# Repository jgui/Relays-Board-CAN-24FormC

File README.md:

# Relays-Board-CAN-24FormC
Board with 24 relays (Form C) controlled by CAN.

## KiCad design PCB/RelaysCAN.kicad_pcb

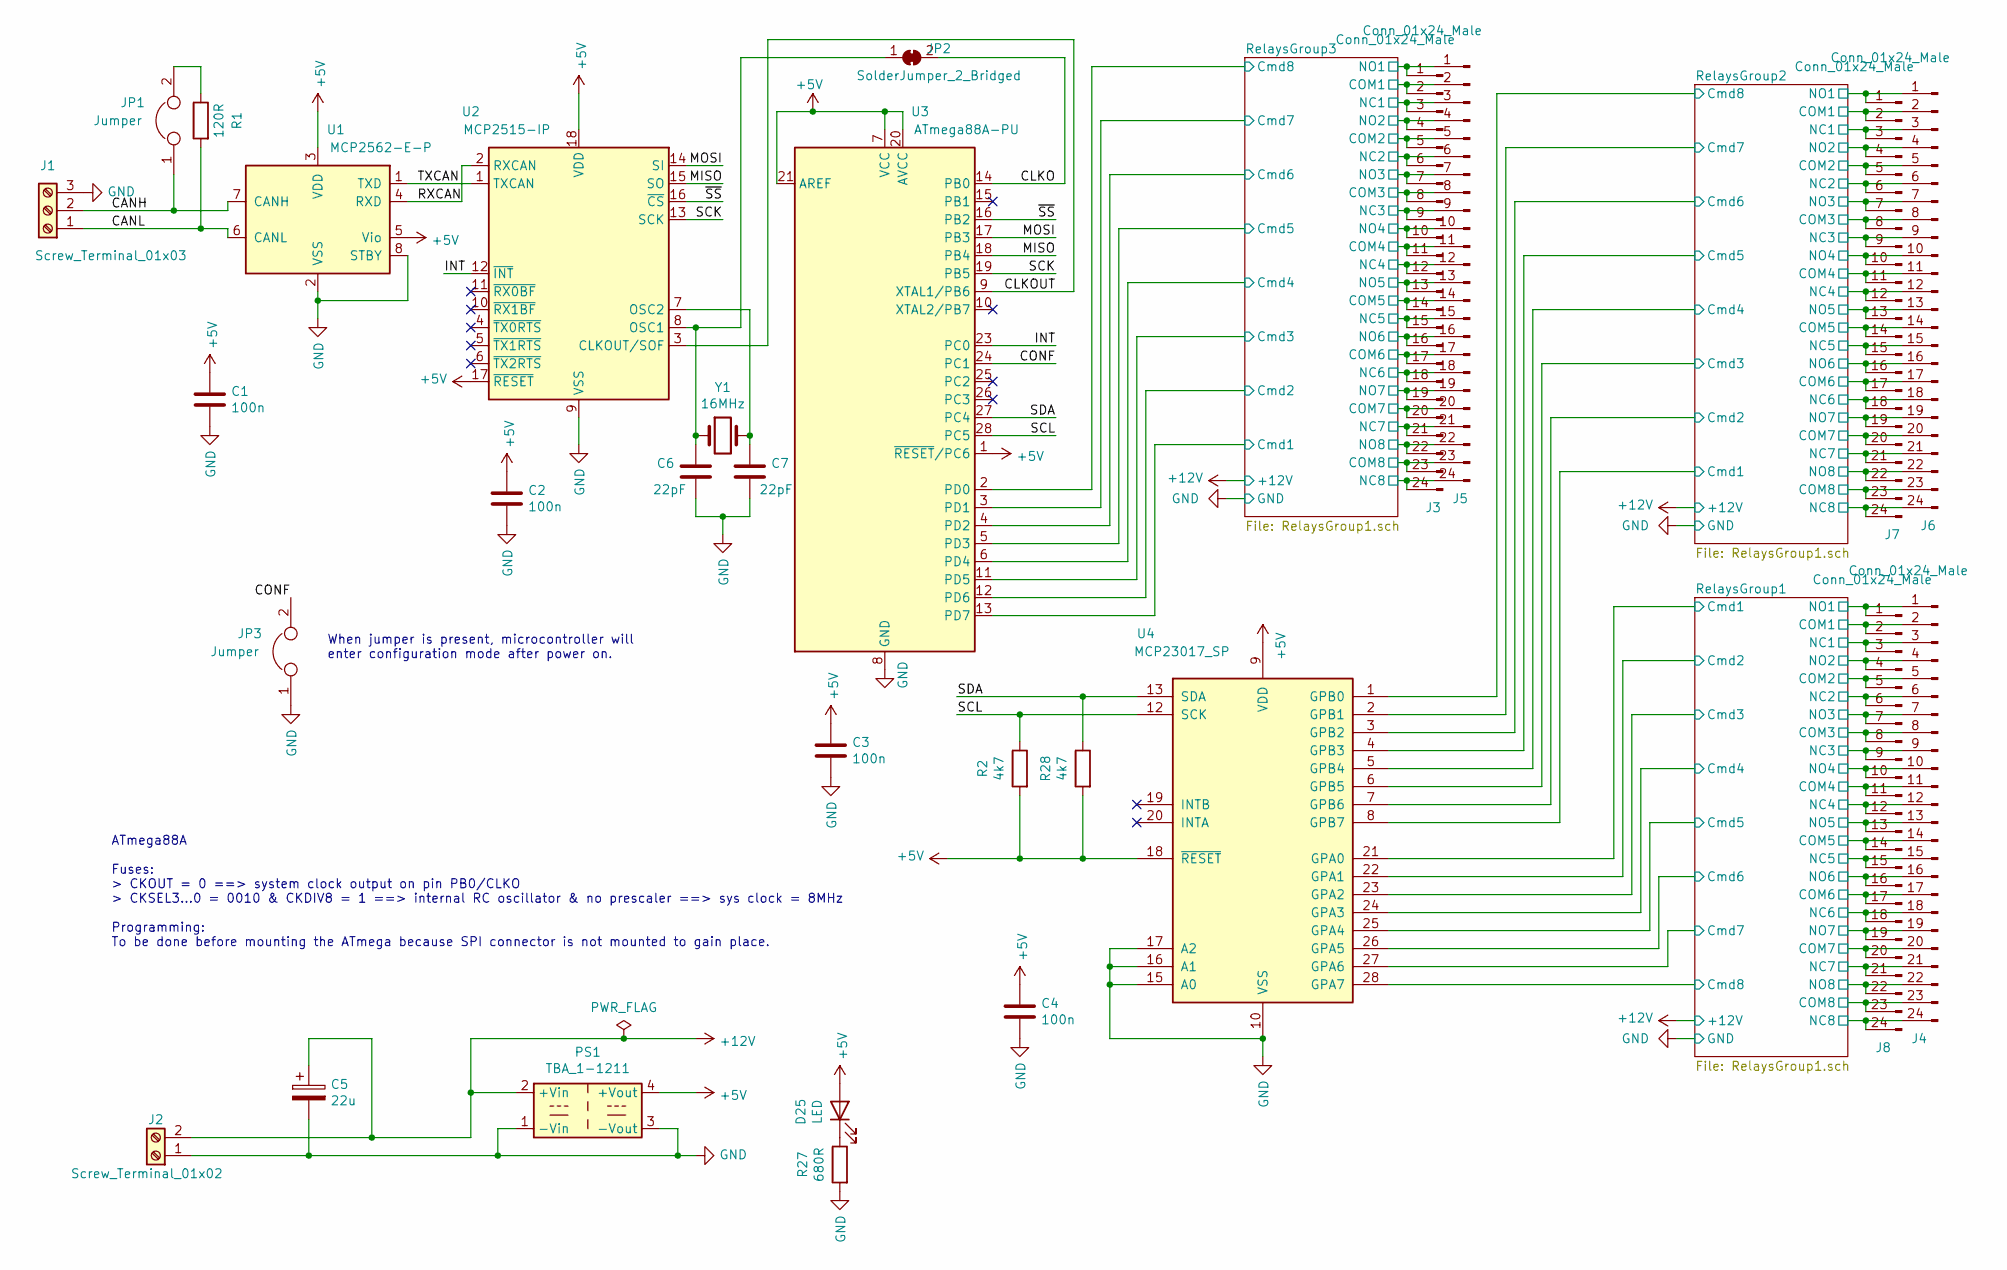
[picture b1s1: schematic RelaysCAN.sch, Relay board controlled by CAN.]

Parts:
C1, C2, C3, C4: 100n; C_Disc_D4.3mm_W1.9mm_P5.00mm
C5: 22u; CP_Radial_D5.0mm_P2.50mm
C6, C7: 22pF; C_Disc_D4.3mm_W1.9mm_P5.00mm
D25: LED; LED_D3.0mm
J1: Screw_Terminal_01x03; TerminalBlock_bornier-3_P5.08mm
J2: Screw_Terminal_01x02; TerminalBlock_bornier-2_P5.08mm
J3, J7, J8: Conn_01x24_Male; DualSideEdge_65x250mils_2.54mmx24pads
J4, J5, J6: Conn_01x24_Male; PinHeader_1x24_P2.54mm_Vertical
JP1, JP3: Jumper; PinHeader_1x02_P2.54mm_Vertical
JP2: SolderJumper_2_Bridged; SolderJumper-2_P1.3mm_Open_RoundedPad1.0x1.5mm
PS1: TBA_1-1211; Converter_DCDC_TRACO_TBA-1-xxxx_Single_THT
R1: 120R; R_Axial_DIN0207_L6.3mm_D2.5mm_P5.08mm_Vertical
R2, R28: 4k7; R_Axial_DIN0207_L6.3mm_D2.5mm_P5.08mm_Vertical
R27: 680R; R_Axial_DIN0207_L6.3mm_D2.5mm_P5.08mm_Vertical
U1: MCP2562-E-P; DIP-8_W7.62mm
U2: MCP2515-IP; DIP-18_W7.62mm_LongPads
U3: ATmega88A-PU; DIP-28_W7.62mm_LongPads
U4: MCP23017_SP; DIP-28_W7.62mm_LongPads
Y1: 16MHz; Crystal_HC18-U_Vertical

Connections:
+5V: C1.1, C2.1, C3.1, C4.1, D25.2 (A), PS1.4 (+Vout), R2.2, R28.2, U1.3 (VDD), U1.5 (Vio), U2.17 (~RESET), U2.18 (VDD), U3.1 (~RESET~/PC6), U3.7 (VCC), U3.20 (AVCC), U3.21 (AREF), U4.9 (VDD), U4.18 (~RESET~)
+12V: C5.1, J2.2, PS1.2 (+Vin); also elsewhere on the board
/CANH: J1.2, JP1.1, U1.7 (CANH)
/CANL: J1.1, R1.2, U1.6 (CANL)
/CLKO: JP2.2 (B), U3.14 (PB0)
/CLKOUT: U2.3 (CLKOUT/SOF), U3.9 (XTAL1/PB6)
/CONF: JP3.2, U3.24 (PC1)
/INT: U2.12 (~INT), U3.23 (PC0)
/MISO: U2.15 (SO), U3.18 (PB4)
/MOSI: U2.14 (SI), U3.17 (PB3)
/RXCAN: U1.4 (RXD), U2.2 (RXCAN)
/RelaysGroup1/COM1: J4.2, J8.2; also elsewhere on the board
/RelaysGroup1/COM2: J4.5, J8.5; also elsewhere on the board
/RelaysGroup1/COM3: J4.8, J8.8; also elsewhere on the board
/RelaysGroup1/COM4: J4.11, J8.11; also elsewhere on the board
/RelaysGroup1/COM5: J4.14, J8.14; also elsewhere on the board
/RelaysGroup1/COM6: J4.17, J8.17; also elsewhere on the board
/RelaysGroup1/COM7: J4.20, J8.20; also elsewhere on the board
/RelaysGroup1/COM8: J4.23, J8.23; also elsewhere on the board
/RelaysGroup1/Cmd1: U4.21 (GPA0); also elsewhere on the board
/RelaysGroup1/Cmd2: U4.22 (GPA1); also elsewhere on the board
/RelaysGroup1/Cmd3: U4.23 (GPA2); also elsewhere on the board
/RelaysGroup1/Cmd4: U4.24 (GPA3); also elsewhere on the board
/RelaysGroup1/Cmd5: U4.25 (GPA4); also elsewhere on the board
/RelaysGroup1/Cmd6: U4.26 (GPA5); also elsewhere on the board
/RelaysGroup1/Cmd7: U4.27 (GPA6); also elsewhere on the board
/RelaysGroup1/Cmd8: U4.28 (GPA7); also elsewhere on the board
/RelaysGroup1/NC1: J4.3, J8.3; also elsewhere on the board
/RelaysGroup1/NC2: J4.6, J8.6; also elsewhere on the board
/RelaysGroup1/NC3: J4.9, J8.9; also elsewhere on the board
/RelaysGroup1/NC4: J4.12, J8.12; also elsewhere on the board
/RelaysGroup1/NC5: J4.15, J8.15; also elsewhere on the board
/RelaysGroup1/NC6: J4.18, J8.18; also elsewhere on the board
/RelaysGroup1/NC7: J4.21, J8.21; also elsewhere on the board
/RelaysGroup1/NC8: J4.24, J8.24; also elsewhere on the board
/RelaysGroup1/NO1: J4.1, J8.1; also elsewhere on the board
/RelaysGroup1/NO2: J4.4, J8.4; also elsewhere on the board
/RelaysGroup1/NO3: J4.7, J8.7; also elsewhere on the board
/RelaysGroup1/NO4: J4.10, J8.10; also elsewhere on the board
/RelaysGroup1/NO5: J4.13, J8.13; also elsewhere on the board
/RelaysGroup1/NO6: J4.16, J8.16; also elsewhere on the board
/RelaysGroup1/NO7: J4.19, J8.19; also elsewhere on the board
/RelaysGroup1/NO8: J4.22, J8.22; also elsewhere on the board
/RelaysGroup2/COM1: J6.2, J7.2; also elsewhere on the board
/RelaysGroup2/COM2: J6.5, J7.5; also elsewhere on the board
/RelaysGroup2/COM3: J6.8, J7.8; also elsewhere on the board
/RelaysGroup2/COM4: J6.11, J7.11; also elsewhere on the board
/RelaysGroup2/COM5: J6.14, J7.14; also elsewhere on the board
/RelaysGroup2/COM6: J6.17, J7.17; also elsewhere on the board
/RelaysGroup2/COM7: J6.20, J7.20; also elsewhere on the board
/RelaysGroup2/COM8: J6.23, J7.23; also elsewhere on the board
/RelaysGroup2/Cmd1: U4.8 (GPB7); also elsewhere on the board
/RelaysGroup2/Cmd2: U4.7 (GPB6); also elsewhere on the board
/RelaysGroup2/Cmd3: U4.6 (GPB5); also elsewhere on the board
/RelaysGroup2/Cmd4: U4.5 (GPB4); also elsewhere on the board
/RelaysGroup2/Cmd5: U4.4 (GPB3); also elsewhere on the board
/RelaysGroup2/Cmd6: U4.3 (GPB2); also elsewhere on the board
/RelaysGroup2/Cmd7: U4.2 (GPB1); also elsewhere on the board
/RelaysGroup2/Cmd8: U4.1 (GPB0); also elsewhere on the board
/RelaysGroup2/NC1: J6.3, J7.3; also elsewhere on the board
/RelaysGroup2/NC2: J6.6, J7.6; also elsewhere on the board
/RelaysGroup2/NC3: J6.9, J7.9; also elsewhere on the board
/RelaysGroup2/NC4: J6.12, J7.12; also elsewhere on the board
/RelaysGroup2/NC5: J6.15, J7.15; also elsewhere on the board
/RelaysGroup2/NC6: J6.18, J7.18; also elsewhere on the board
/RelaysGroup2/NC7: J6.21, J7.21; also elsewhere on the board
/RelaysGroup2/NC8: J6.24, J7.24; also elsewhere on the board
/RelaysGroup2/NO1: J6.1, J7.1; also elsewhere on the board
/RelaysGroup2/NO2: J6.4, J7.4; also elsewhere on the board
/RelaysGroup2/NO3: J6.7, J7.7; also elsewhere on the board
/RelaysGroup2/NO4: J6.10, J7.10; also elsewhere on the board
/RelaysGroup2/NO5: J6.13, J7.13; also elsewhere on the board
/RelaysGroup2/NO6: J6.16, J7.16; also elsewhere on the board
/RelaysGroup2/NO7: J6.19, J7.19; also elsewhere on the board
/RelaysGroup2/NO8: J6.22, J7.22; also elsewhere on the board
/RelaysGroup3/COM1: J3.2, J5.2; also elsewhere on the board
/RelaysGroup3/COM2: J3.5, J5.5; also elsewhere on the board
/RelaysGroup3/COM3: J3.8, J5.8; also elsewhere on the board
/RelaysGroup3/COM4: J3.11, J5.11; also elsewhere on the board
/RelaysGroup3/COM5: J3.14, J5.14; also elsewhere on the board
/RelaysGroup3/COM6: J3.17, J5.17; also elsewhere on the board
/RelaysGroup3/COM7: J3.20, J5.20; also elsewhere on the board
/RelaysGroup3/COM8: J3.23, J5.23; also elsewhere on the board
/RelaysGroup3/Cmd1: U3.13 (PD7); also elsewhere on the board
/RelaysGroup3/Cmd2: U3.12 (PD6); also elsewhere on the board
/RelaysGroup3/Cmd3: U3.11 (PD5); also elsewhere on the board
/RelaysGroup3/Cmd4: U3.6 (PD4); also elsewhere on the board
/RelaysGroup3/Cmd5: U3.5 (PD3); also elsewhere on the board
/RelaysGroup3/Cmd6: U3.4 (PD2); also elsewhere on the board
/RelaysGroup3/Cmd7: U3.3 (PD1); also elsewhere on the board
/RelaysGroup3/Cmd8: U3.2 (PD0); also elsewhere on the board
/RelaysGroup3/NC1: J3.3, J5.3; also elsewhere on the board
/RelaysGroup3/NC2: J3.6, J5.6; also elsewhere on the board
/RelaysGroup3/NC3: J3.9, J5.9; also elsewhere on the board
/RelaysGroup3/NC4: J3.12, J5.12; also elsewhere on the board
/RelaysGroup3/NC5: J3.15, J5.15; also elsewhere on the board
/RelaysGroup3/NC6: J3.18, J5.18; also elsewhere on the board
/RelaysGroup3/NC7: J3.21, J5.21; also elsewhere on the board
/RelaysGroup3/NC8: J3.24, J5.24; also elsewhere on the board
/RelaysGroup3/NO1: J3.1, J5.1; also elsewhere on the board
/RelaysGroup3/NO2: J3.4, J5.4; also elsewhere on the board
/RelaysGroup3/NO3: J3.7, J5.7; also elsewhere on the board
/RelaysGroup3/NO4: J3.10, J5.10; also elsewhere on the board
/RelaysGroup3/NO5: J3.13, J5.13; also elsewhere on the board
/RelaysGroup3/NO6: J3.16, J5.16; also elsewhere on the board
/RelaysGroup3/NO7: J3.19, J5.19; also elsewhere on the board
/RelaysGroup3/NO8: J3.22, J5.22; also elsewhere on the board
/SCK: U2.13 (SCK), U3.19 (PB5)
/SCL: R2.1, U3.28 (PC5), U4.12 (SCK)
/SDA: R28.1, U3.27 (PC4), U4.13 (SDA)
/TXCAN: U1.1 (TXD), U2.1 (TXCAN)
/~SS: U2.16 (~CS), U3.16 (PB2)
GND: C1.2, C2.2, C3.2, C4.2, C5.2, C6.2, C7.2, J1.3, J2.1, JP3.1, PS1.1 (-Vin), PS1.3 (-Vout), R27.2, U1.2 (VSS), U1.8 (STBY), U2.9 (VSS), U3.8 (GND), U3.22 (GND), U4.10 (VSS), U4.15 (A0), U4.16 (A1), U4.17 (A2); also elsewhere on the board
unnamed: C6.1, JP2.1 (A), U2.8 (OSC1), Y1.1
unnamed: C7.1, U2.7 (OSC2), Y1.2
unnamed: D25.1 (K), R27.1
unnamed: JP1.2, R1.1

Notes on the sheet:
ATmega88A Fuses: > CKOUT = 0 ==> system clock output on pin PB0/CLKO > CKSEL3...0 = 0010 & CKDIV8 = 1 ==> internal RC oscillator & no prescaler ==> sys clock = 8MHz Programming: To be done before mounting the ATmega because SPI connector is not mounted to gain place.
When jumper is present, microcontroller will enter configuration mode after power on.

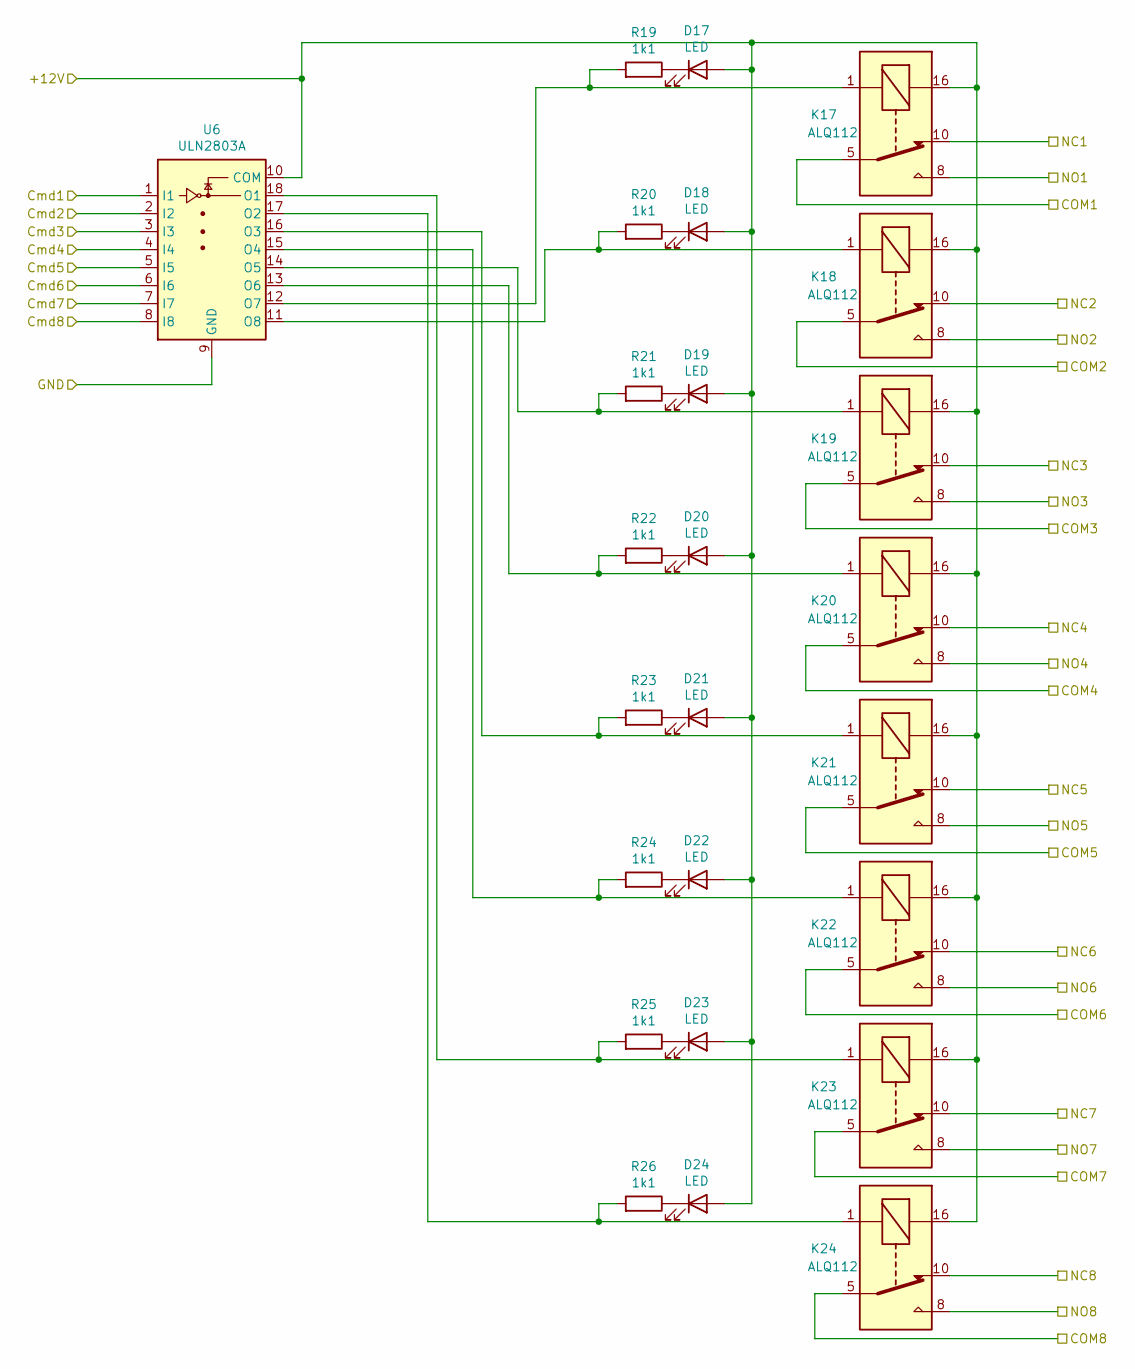
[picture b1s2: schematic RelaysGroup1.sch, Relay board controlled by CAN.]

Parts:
D1, D2, D3, D4, D5, D6, D7, D8: LED; LED_D3.0mm
K1, K2, K3, K4, K5, K6, K7, K8: ALQ112; Relay_Panasonic_ALQ112
R3, R4, R5, R6, R7, R8, R9, R10: 1k1; R_Axial_DIN0207_L6.3mm_D2.5mm_P5.08mm_Vertical
U7: ULN2803A; DIP-18_W7.62mm_LongPads

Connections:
+12V: D1.2 (A), D2.2 (A), D3.2 (A), D4.2 (A), D5.2 (A), D6.2 (A), D7.2 (A), D8.2 (A), K1.16, K2.16, K3.16, K4.16, K5.16, K6.16, K7.16, K8.16, U7.10 (COM); also elsewhere on the board
/RelaysGroup1/COM1: K1.5; also elsewhere on the board
/RelaysGroup1/COM2: K2.5; also elsewhere on the board
/RelaysGroup1/COM3: K3.5; also elsewhere on the board
/RelaysGroup1/COM4: K4.5; also elsewhere on the board
/RelaysGroup1/COM5: K5.5; also elsewhere on the board
/RelaysGroup1/COM6: K6.5; also elsewhere on the board
/RelaysGroup1/COM7: K7.5; also elsewhere on the board
/RelaysGroup1/COM8: K8.5; also elsewhere on the board
/RelaysGroup1/Cmd1: U7.1 (I1); also elsewhere on the board
/RelaysGroup1/Cmd2: U7.2 (I2); also elsewhere on the board
/RelaysGroup1/Cmd3: U7.3 (I3); also elsewhere on the board
/RelaysGroup1/Cmd4: U7.4 (I4); also elsewhere on the board
/RelaysGroup1/Cmd5: U7.5 (I5); also elsewhere on the board
/RelaysGroup1/Cmd6: U7.6 (I6); also elsewhere on the board
/RelaysGroup1/Cmd7: U7.7 (I7); also elsewhere on the board
/RelaysGroup1/Cmd8: U7.8 (I8); also elsewhere on the board
/RelaysGroup1/NC1: K1.10; also elsewhere on the board
/RelaysGroup1/NC2: K2.10; also elsewhere on the board
/RelaysGroup1/NC3: K3.10; also elsewhere on the board
/RelaysGroup1/NC4: K4.10; also elsewhere on the board
/RelaysGroup1/NC5: K5.10; also elsewhere on the board
/RelaysGroup1/NC6: K6.10; also elsewhere on the board
/RelaysGroup1/NC7: K7.10; also elsewhere on the board
/RelaysGroup1/NC8: K8.10; also elsewhere on the board
/RelaysGroup1/NO1: K1.8; also elsewhere on the board
/RelaysGroup1/NO2: K2.8; also elsewhere on the board
/RelaysGroup1/NO3: K3.8; also elsewhere on the board
/RelaysGroup1/NO4: K4.8; also elsewhere on the board
/RelaysGroup1/NO5: K5.8; also elsewhere on the board
/RelaysGroup1/NO6: K6.8; also elsewhere on the board
/RelaysGroup1/NO7: K7.8; also elsewhere on the board
/RelaysGroup1/NO8: K8.8; also elsewhere on the board
GND: U7.9 (GND); also elsewhere on the board
unnamed: D1.1 (K), R3.1
unnamed: D2.1 (K), R4.1
unnamed: D3.1 (K), R5.1
unnamed: D4.1 (K), R6.1
unnamed: D5.1 (K), R7.1
unnamed: D6.1 (K), R8.1
unnamed: D7.1 (K), R9.1
unnamed: D8.1 (K), R10.1
unnamed: K1.1, R3.2, U7.12 (O7)
unnamed: K2.1, R4.2, U7.11 (O8)
unnamed: K3.1, R5.2, U7.14 (O5)
unnamed: K4.1, R6.2, U7.13 (O6)
unnamed: K5.1, R7.2, U7.16 (O3)
unnamed: K6.1, R8.2, U7.15 (O4)
unnamed: K7.1, R9.2, U7.18 (O1)
unnamed: K8.1, R10.2, U7.17 (O2)

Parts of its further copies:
D9, D10, D11, D12, D13, D14, D15, D16, D17, D18, D19, D20, D21, D22, D23, D24: LED; LED_D3.0mm
K9, K10, K11, K12, K13, K14, K15, K16, K17, K18, K19, K20, K21, K22, K23, K24: ALQ112; Relay_Panasonic_ALQ112
R11, R12, R13, R14, R15, R16, R17, R18, R19, R20, R21, R22, R23, R24, R25, R26: 1k1; R_Axial_DIN0207_L6.3mm_D2.5mm_P5.08mm_Vertical
U5, U6: ULN2803A; DIP-18_W7.62mm_LongPads

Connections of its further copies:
+12V: D9.2 (A), D10.2 (A), D11.2 (A), D12.2 (A), D13.2 (A), D14.2 (A), D15.2 (A), D16.2 (A), D17.2 (A), D18.2 (A), D19.2 (A), D20.2 (A), D21.2 (A), D22.2 (A), D23.2 (A), D24.2 (A), K9.16, K10.16, K11.16, K12.16, K13.16, K14.16, K15.16, K16.16, K17.16, K18.16, K19.16, K20.16, K21.16, K22.16, K23.16, K24.16, U5.10 (COM), U6.10 (COM); also elsewhere on the board
/RelaysGroup2/COM1: K9.5; also elsewhere on the board
/RelaysGroup2/COM2: K10.5; also elsewhere on the board
/RelaysGroup2/COM3: K11.5; also elsewhere on the board
/RelaysGroup2/COM4: K12.5; also elsewhere on the board
/RelaysGroup2/COM5: K13.5; also elsewhere on the board
/RelaysGroup2/COM6: K14.5; also elsewhere on the board
/RelaysGroup2/COM7: K15.5; also elsewhere on the board
/RelaysGroup2/COM8: K16.5; also elsewhere on the board
/RelaysGroup2/Cmd1: U5.1 (I1); also elsewhere on the board
/RelaysGroup2/Cmd2: U5.2 (I2); also elsewhere on the board
/RelaysGroup2/Cmd3: U5.3 (I3); also elsewhere on the board
/RelaysGroup2/Cmd4: U5.4 (I4); also elsewhere on the board
/RelaysGroup2/Cmd5: U5.5 (I5); also elsewhere on the board
/RelaysGroup2/Cmd6: U5.6 (I6); also elsewhere on the board
/RelaysGroup2/Cmd7: U5.7 (I7); also elsewhere on the board
/RelaysGroup2/Cmd8: U5.8 (I8); also elsewhere on the board
/RelaysGroup2/NC1: K9.10; also elsewhere on the board
/RelaysGroup2/NC2: K10.10; also elsewhere on the board
/RelaysGroup2/NC3: K11.10; also elsewhere on the board
/RelaysGroup2/NC4: K12.10; also elsewhere on the board
/RelaysGroup2/NC5: K13.10; also elsewhere on the board
/RelaysGroup2/NC6: K14.10; also elsewhere on the board
/RelaysGroup2/NC7: K15.10; also elsewhere on the board
/RelaysGroup2/NC8: K16.10; also elsewhere on the board
/RelaysGroup2/NO1: K9.8; also elsewhere on the board
/RelaysGroup2/NO2: K10.8; also elsewhere on the board
/RelaysGroup2/NO3: K11.8; also elsewhere on the board
/RelaysGroup2/NO4: K12.8; also elsewhere on the board
/RelaysGroup2/NO5: K13.8; also elsewhere on the board
/RelaysGroup2/NO6: K14.8; also elsewhere on the board
/RelaysGroup2/NO7: K15.8; also elsewhere on the board
/RelaysGroup2/NO8: K16.8; also elsewhere on the board
/RelaysGroup3/COM1: K17.5; also elsewhere on the board
/RelaysGroup3/COM2: K18.5; also elsewhere on the board
/RelaysGroup3/COM3: K19.5; also elsewhere on the board
/RelaysGroup3/COM4: K20.5; also elsewhere on the board
/RelaysGroup3/COM5: K21.5; also elsewhere on the board
/RelaysGroup3/COM6: K22.5; also elsewhere on the board
/RelaysGroup3/COM7: K23.5; also elsewhere on the board
/RelaysGroup3/COM8: K24.5; also elsewhere on the board
/RelaysGroup3/Cmd1: U6.1 (I1); also elsewhere on the board
/RelaysGroup3/Cmd2: U6.2 (I2); also elsewhere on the board
/RelaysGroup3/Cmd3: U6.3 (I3); also elsewhere on the board
/RelaysGroup3/Cmd4: U6.4 (I4); also elsewhere on the board
/RelaysGroup3/Cmd5: U6.5 (I5); also elsewhere on the board
/RelaysGroup3/Cmd6: U6.6 (I6); also elsewhere on the board
/RelaysGroup3/Cmd7: U6.7 (I7); also elsewhere on the board
/RelaysGroup3/Cmd8: U6.8 (I8); also elsewhere on the board
/RelaysGroup3/NC1: K17.10; also elsewhere on the board
/RelaysGroup3/NC2: K18.10; also elsewhere on the board
/RelaysGroup3/NC3: K19.10; also elsewhere on the board
/RelaysGroup3/NC4: K20.10; also elsewhere on the board
/RelaysGroup3/NC5: K21.10; also elsewhere on the board
/RelaysGroup3/NC6: K22.10; also elsewhere on the board
/RelaysGroup3/NC7: K23.10; also elsewhere on the board
/RelaysGroup3/NC8: K24.10; also elsewhere on the board
/RelaysGroup3/NO1: K17.8; also elsewhere on the board
/RelaysGroup3/NO2: K18.8; also elsewhere on the board
/RelaysGroup3/NO3: K19.8; also elsewhere on the board
/RelaysGroup3/NO4: K20.8; also elsewhere on the board
/RelaysGroup3/NO5: K21.8; also elsewhere on the board
/RelaysGroup3/NO6: K22.8; also elsewhere on the board
/RelaysGroup3/NO7: K23.8; also elsewhere on the board
/RelaysGroup3/NO8: K24.8; also elsewhere on the board
GND: U5.9 (GND), U6.9 (GND); also elsewhere on the board
unnamed: D9.1 (K), R11.1
unnamed: D10.1 (K), R12.1
unnamed: D11.1 (K), R13.1
unnamed: D12.1 (K), R14.1
unnamed: D13.1 (K), R15.1
unnamed: D14.1 (K), R16.1
unnamed: D15.1 (K), R17.1
unnamed: D16.1 (K), R18.1
unnamed: D17.1 (K), R19.1
unnamed: D18.1 (K), R20.1
unnamed: D19.1 (K), R21.1
unnamed: D20.1 (K), R22.1
unnamed: D21.1 (K), R23.1
unnamed: D22.1 (K), R24.1
unnamed: D23.1 (K), R25.1
unnamed: D24.1 (K), R26.1
unnamed: K9.1, R11.2, U5.12 (O7)
unnamed: K10.1, R12.2, U5.11 (O8)
unnamed: K11.1, R13.2, U5.14 (O5)
unnamed: K12.1, R14.2, U5.13 (O6)
unnamed: K13.1, R15.2, U5.16 (O3)
unnamed: K14.1, R16.2, U5.15 (O4)
unnamed: K15.1, R17.2, U5.18 (O1)
unnamed: K16.1, R18.2, U5.17 (O2)
unnamed: K17.1, R19.2, U6.12 (O7)
unnamed: K18.1, R20.2, U6.11 (O8)
unnamed: K19.1, R21.2, U6.14 (O5)
unnamed: K20.1, R22.2, U6.13 (O6)
unnamed: K21.1, R23.2, U6.16 (O3)
unnamed: K22.1, R24.2, U6.15 (O4)
unnamed: K23.1, R25.2, U6.18 (O1)
unnamed: K24.1, R26.2, U6.17 (O2)

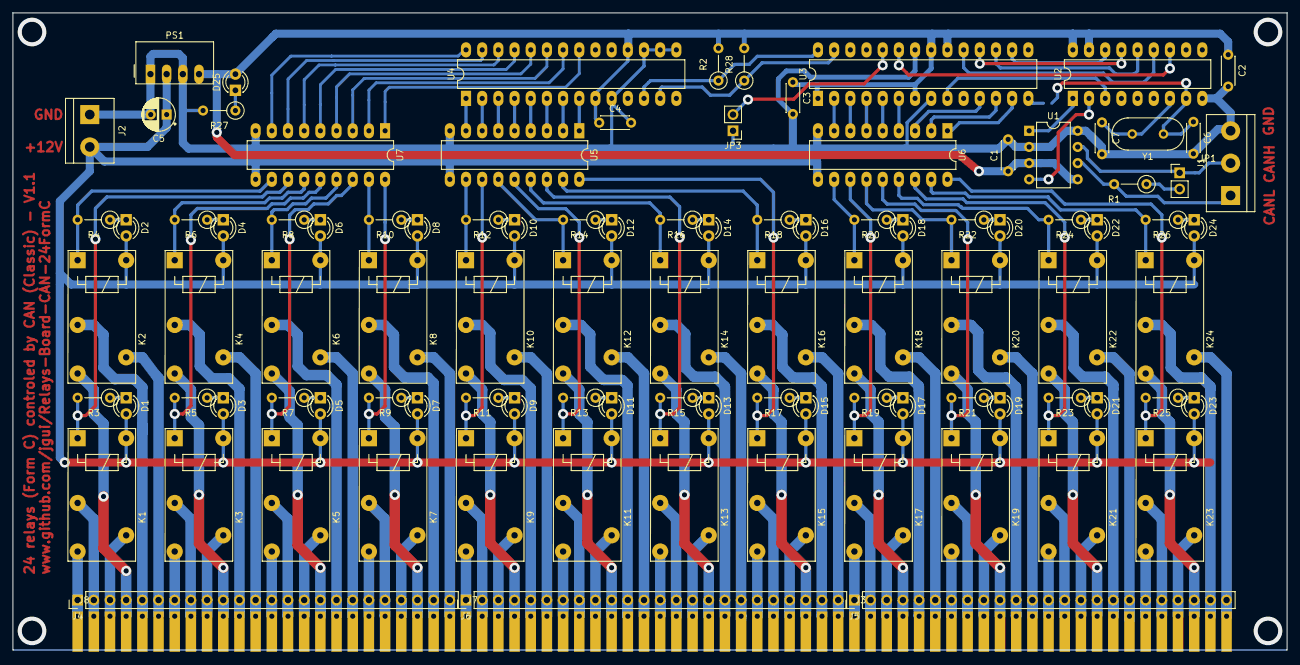
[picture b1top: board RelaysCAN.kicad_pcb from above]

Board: 2 copper layers, 200.0 x 100.0 mm, 104 parts (1 on the bottom side), 165 nets.

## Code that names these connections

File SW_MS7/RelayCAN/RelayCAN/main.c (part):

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//______________________________________________________________________________
// Configuration mode

#define ModeIsConf() (!(PINC & (1 << PC1)))


//______________________________________________________________________________
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{
	// Setup ports
	/*
	PB0		CLKO	IN	Pull-up		Not used (disconnected from MCP2515 OSC1) => input with pull-up
	PB1		NC		IN	Pull-up		
	PB2		SS		OUT	High		SPI module will anyway configure this pin		
	PB3		MOSI	OUT	Low			SPI module will anyway configure this pin		
	PB4		MISO	IN				SPI module will anyway configure this pin	
	PB5		SCK		OUT	Low			SPI module will anyway configure this pin	
	PB6		XTAL1	IN				Micro is clocked from MCP2515
	PB7		NC		IN	Pull-up
	
	PC0		INT		IN				
	PC1		CONF	IN	Pull-up
	PC2		NC		IN	Pull-up
	PC3		LED		OUT	Low			LED is not mounted on PCB, only used for debug
	PC4		SDA		IN				I2C module will anyway configure this pin
	PC5		SCL		IN				I2C module will anyway configure this pin
	PC6		RESET	IN				
	
	PD0		Cmd8	OUT	Low			Relay Group 3
	PD1		Cmd7	OUT	Low			Relay Group 3
	PD2		Cmd6	OUT	Low			Relay Group 3
	PD3		Cmd5	OUT	Low			Relay Group 3
	PD4		Cmd4	OUT	Low			Relay Group 3
	PD5		Cmd3	OUT	Low			Relay Group 3
	PD6		Cmd2	OUT	Low			Relay Group 3
	PD7		Cmd1	OUT	Low			Relay Group 3
	*/
	
	// Set direction (1 = output, 0 = input)
	DDRB  = (0<<PB7)|(0<<PB6)|(1<<PB5)|(0<<PB4)|(1<<PB3)|(1<<PB2)|(0<<PB1)|(0<<PB0);
	DDRC  =          (0<<PC6)|(0<<PC5)|(0<<PC4)|(1<<PC3)|(0<<PC2)|(0<<PC1)|(0<<PC0);
	DDRD  = (1<<PD7)|(1<<PD6)|(1<<PD5)|(1<<PD4)|(1<<PD3)|(1<<PD2)|(1<<PD1)|(1<<PD0);
	
	// Set pull-ups or outputs high (1), or, no pull-ups or outputs low (0)
	PORTB = (1<<PB7)|(0<<PB6)|(0<<PB5)|(0<<PB4)|(0<<PB3)|(1<<PB2)|(1<<PB1)|(1<<PB0);
	PORTC =          (0<<PC6)|(0<<PC5)|(0<<PC4)|(0<<PC3)|(1<<PC2)|(1<<PC1)|(0<<PC0);
	PORTD = (0<<PD7)|(0<<PD6)|(0<<PD5)|(0<<PD4)|(0<<PD3)|(0<<PD2)|(0<<PD1)|(0<<PD0);
	

	#ifdef DEBUG
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
/*
Relay, Port		Relay, Port		Relay, Port
1	GPA6		9	GPB1		17	PD1
2	GPA7		10	GPB0		18	PD0
3	GPA4		11	GPB3		19	PD3
4	GPA5		12	GPB2		20	PD2
5	GPA2		13	GPB5		21	PD5
6	GPA3		14	GPB4		22	PD4
7	GPA0		15	GPB7		23	PD7
8	GPA1		16	GPB6		24	PD6
*/
void relay_update(void)
{
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
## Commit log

2021-06-27 Add PCB.
2021-07-17 Update PCB.
2021-08-17 Add the software for the micro-controller.
2021-08-17 Add a jumper to enter configuration mode.
2021-09-15 Add Configuration Mode to software.
